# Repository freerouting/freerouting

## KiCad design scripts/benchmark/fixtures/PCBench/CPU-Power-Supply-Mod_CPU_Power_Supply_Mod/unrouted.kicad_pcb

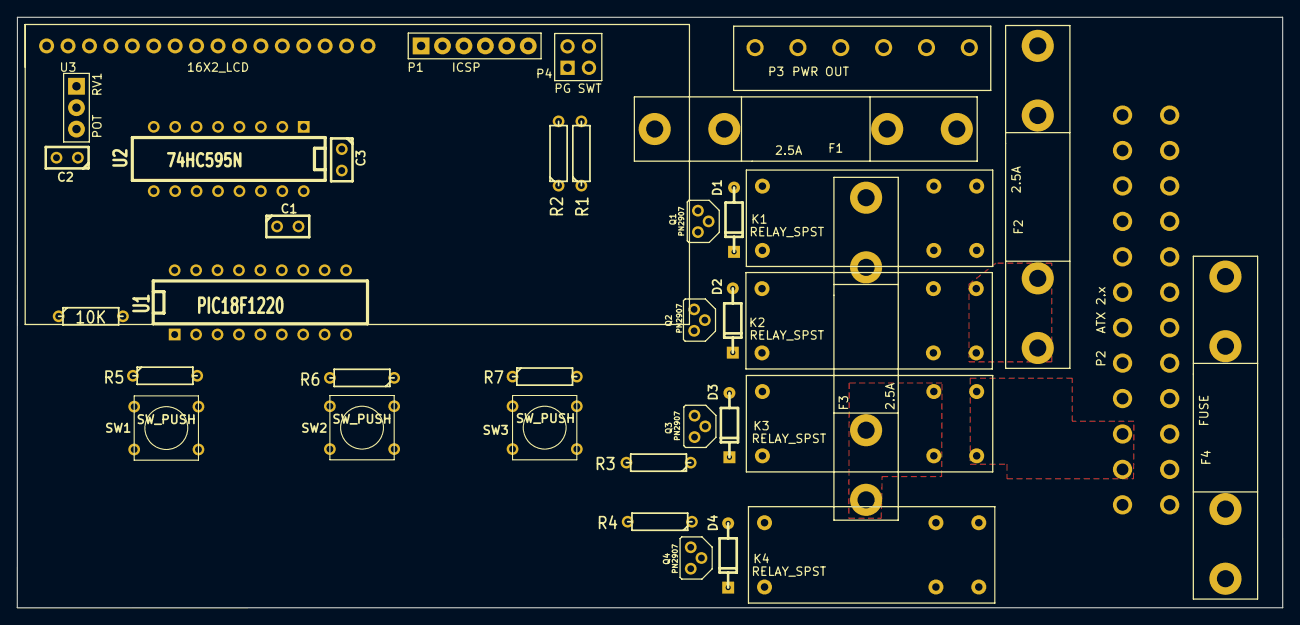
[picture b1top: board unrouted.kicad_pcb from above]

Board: 2 copper layers, 150.0 x 70.0 mm, 38 parts (0 on the bottom side), 49 nets, no tracks yet.

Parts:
C1, C2, C3: 100n; C1
D1, D2, D3, D4: DIODE; DO-35
F1, F2, F3: 2.5A; FUSE
F4: FUSE
K1, K2, K3, K4: RELAY_SPST
P1: ICSP; CON_6x1
P2: ATX 2.x; ATX-24PIN
P3: PWR OUT; 1.27mm_CON
P4: PG SWT; CON_2x2
Q1, Q2, Q3, Q4: PN2907; TO92PN
R1, R2, R3, R4, R5, R6, R7: R; R3
R8: 10K; R3
RV1: POT; CON_3x1
SW1, SW2, SW3: SW_PUSH; SW_PUSH_SMALL
U1: PIC18F1220; DIP-18__300
U2: 74HC595N; DIP-16__300
U3: 16X2_LCD; 1602A_LCD

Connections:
+3.3V: K1.2, P2.1, P2.2, P2.12, P2.13
+5V: F2.1, P2.4, P2.6, P2.21, P2.22, P2.23
+5VA: C1.1, C2.2, C3.2, P1.2, P2.9, Q1.1, Q2.1, Q3.1, Q4.1, R8.1, RV1.1, SW1.1, SW2.1, SW3.1, U1.14, U2.10, U2.16, U3.2, U3.15
+12V: K3.2, P2.10, P2.11
-12V: F4.1, P2.14
/ON1: Q1.2, R1.1
/ON2: Q2.2, R2.1
/ON3: Q3.2, R3.1
/ON4: Q4.2, R4.1
/PG: P2.8, U1.7
/PGC: P1.5, P4.3, U1.12
/PGD: P1.4, P4.1, U1.13
/PN: P2.16, U1.6
/SW1: R5.2, SW1.2, U1.1
/SW2: R6.2, SW2.2, U1.2
/SW3: R7.2, SW3.2, U1.3
GND: C1.2, C2.1, C3.1, D1.1, D2.1, D3.1, D4.1, K1.3, K2.3, K3.3, K4.3, P1.3, P2.3, P2.5, P2.7, P2.15, P2.17, P2.18, P2.19, P2.24, P3.1, P3.4, R5.1, R6.1, R7.1, RV1.3, U1.5, U2.8, U2.13, U3.1, U3.16
unnamed: P1.1, R8.2, U1.4
unnamed: RV1.2, U3.3
unnamed: U2.15, U3.14
unnamed: U2.1, U3.13
unnamed: U2.2, U3.12
unnamed: U2.3, U3.11
unnamed: U2.4, U3.10
unnamed: U2.5, U3.9
unnamed: U2.6, U3.8
unnamed: U2.7, U3.7
unnamed: U1.18, U3.6
unnamed: U1.10, U3.4
unnamed: U1.11, U3.5
unnamed: U1.15, U2.14
unnamed: U1.16, U2.12
unnamed: U1.17, U2.11
unnamed: F3.1, P3.3
unnamed: F2.2, K2.2
unnamed: P4.4, R2.2
unnamed: P4.2, R1.2
unnamed: D3.2, K3.4, Q3.3
unnamed: F4.2, K4.2
unnamed: D4.2, K4.4, Q4.3
unnamed: K4.1, P3.6
unnamed: D2.2, K2.4, Q2.3
unnamed: D1.2, K1.4, Q1.3
unnamed: F1.1, P3.2
unnamed: R4.2, U1.8
unnamed: R3.2, U1.9
unnamed: F1.2, K1.1
unnamed: K2.1, P3.5
unnamed: F3.2, K3.1

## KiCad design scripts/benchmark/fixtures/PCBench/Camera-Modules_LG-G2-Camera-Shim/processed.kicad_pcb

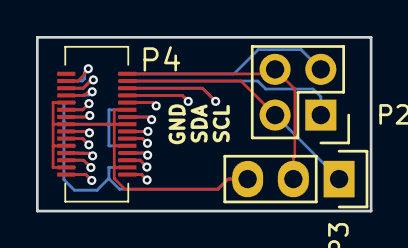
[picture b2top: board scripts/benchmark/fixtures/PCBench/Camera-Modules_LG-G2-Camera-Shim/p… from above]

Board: 2 copper layers, 18.5 x 9.7 mm, 4 parts (1 on the bottom side), 24 nets.

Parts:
P1: LG-G2-G3-Rear-Camera; GB042-30P
P2: CONN_02X02; Pin_Header_Straight_2x02
P3: CONN_01X03; Pin_Header_Straight_1x03
P4: LG-G2-G3-Rear-Camera; GB042-30S

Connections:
/+1V0_VREG_L3: P1.28, P4.28
/+1V8_13M_VCM: P1.3, P4.3
/+1V8_13M_VDDIO: P1.27, P4.27
/+2V7_13M_ANA: P1.16, P4.16
/+2V8_OIS_ANA: P1.15, P4.15
/+2V8_OIS_DIG: P1.4, P4.4
/CAM_MCLK: P1.24, P4.24
/CAM_RESET_N: P1.26, P4.26
/CAM_SCL: P2.2, P3.1, P4.29
/CAM_SDA: P2.4, P3.2, P4.30
/CLK_N: P1.13, P4.13
/CLK_P: P1.12, P4.12
/DATA0_N: P1.10, P4.10
/DATA0_P: P1.9, P4.9
/DATA1_N: P1.7, P4.7
/DATA1_P: P1.6, P4.6
/DATA2_N: P1.18, P4.18
/DATA2_P: P1.19, P4.19
/DATA3_N: P1.21, P4.21
/DATA3_P: P1.22, P4.22
/OIS_RESET_N: P1.2, P4.2
/PHONE_SCL: P1.29, P2.1
/PHONE_SDA: P1.30, P2.3
GND: P1.5, P1.8, P1.11, P1.14, P1.17, P1.20, P1.23, P1.25, P3.3, P4.5, P4.8, P4.11, P4.14, P4.17, P4.20, P4.23, P4.25

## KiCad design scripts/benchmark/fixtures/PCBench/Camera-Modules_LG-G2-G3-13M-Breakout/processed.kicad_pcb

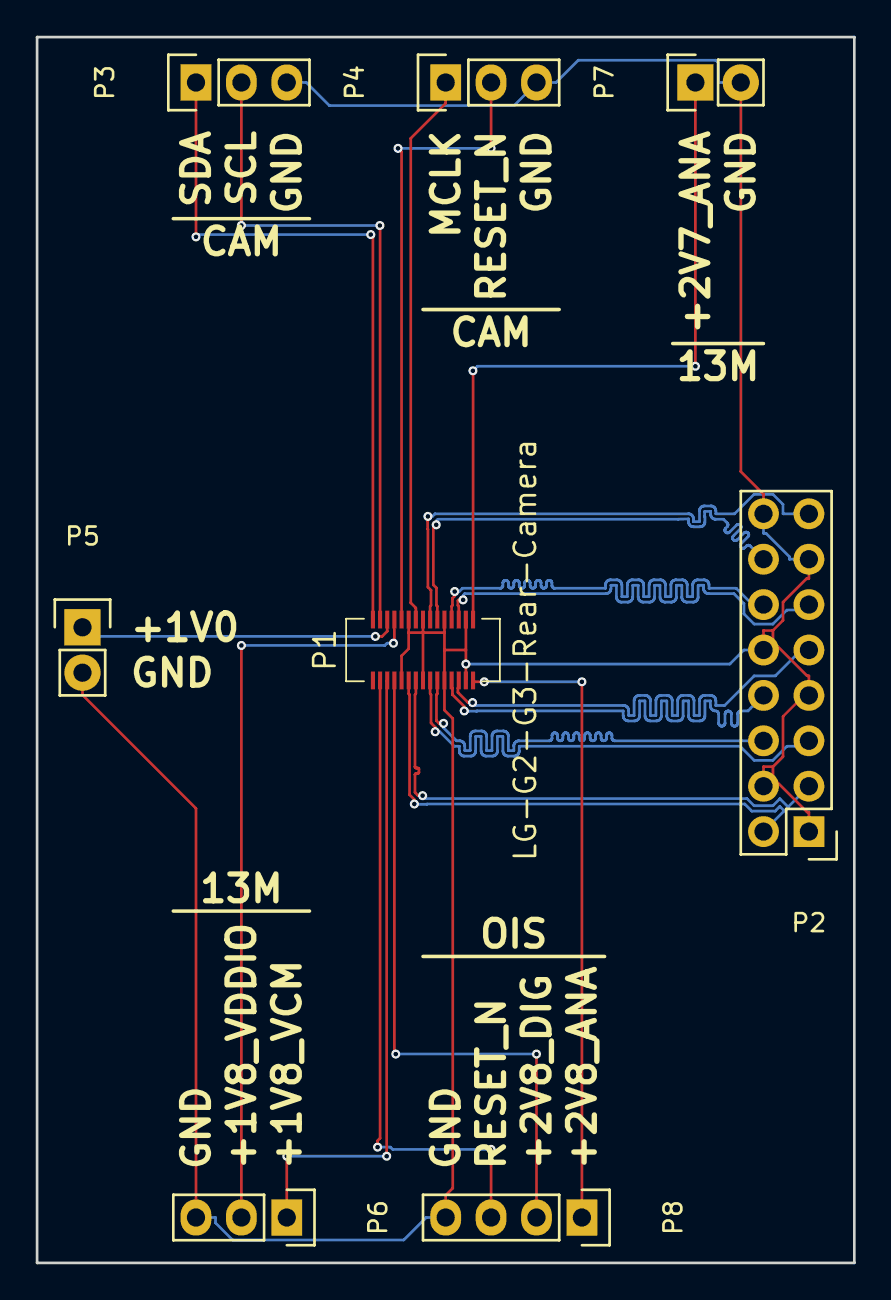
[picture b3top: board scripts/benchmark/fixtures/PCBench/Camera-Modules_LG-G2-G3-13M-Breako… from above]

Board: 2 copper layers, 45.7 x 68.6 mm, 8 parts (0 on the bottom side), 22 nets.

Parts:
P1: LG-G2-G3-Rear-Camera; GB042-30S
P2: CONN_02X08; Pin_Header_Straight_2x08
P3, P4, P6: CONN_01X03; Pin_Header_Straight_1x03
P5, P7: CONN_01X02; Pin_Header_Straight_1x02
P8: CONN_01X04; Pin_Header_Straight_1x04

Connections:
/+1V0_VREG_L3: P1.28, P5.1
/+1V8_13M_VCM: P1.3, P6.1
/+1V8_13M_VDDIO: P1.27, P6.2
/+2V7_13M_ANA: P1.16, P7.1
/+2V8_OIS_ANA: P1.15, P8.1
/+2V8_OIS_DIG: P1.4, P8.2
/CAM_MCLK: P1.24, P4.1
/CAM_RESET_N: P1.26, P4.2
/CAM_SCL: P1.29, P3.2
/CAM_SDA: P1.30, P3.1
/CLK_N: P1.13, P2.9
/CLK_P: P1.12, P2.8
/DATA0_N: P1.10, P2.6
/DATA0_P: P1.9, P2.5
/DATA1_N: P1.7, P2.3
/DATA1_P: P1.6, P2.2
/DATA2_N: P1.18, P2.11
/DATA2_P: P1.19, P2.12
/DATA3_N: P1.21, P2.14
/DATA3_P: P1.22, P2.15
/OIS_RESET_N: P1.2, P8.3
GND: P1.5, P1.8, P1.11, P1.14, P1.17, P1.20, P1.23, P1.25, P2.1, P2.4, P2.7, P2.10, P2.13, P2.16, P3.3, P4.3, P5.2, P6.3, P7.2, P8.4

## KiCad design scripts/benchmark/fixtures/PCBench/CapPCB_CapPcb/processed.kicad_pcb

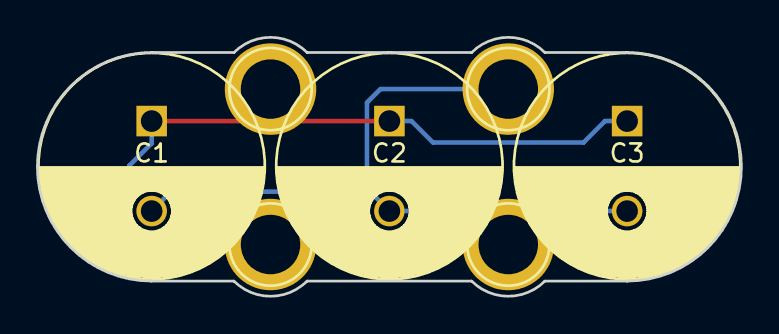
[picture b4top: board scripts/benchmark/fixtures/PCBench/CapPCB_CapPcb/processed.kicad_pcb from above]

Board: 2 copper layers, 39.1 x 14.4 mm, 7 parts (0 on the bottom side), 2 nets.

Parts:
C1, C2, C3: 560uF, 63V; C_Radial_D12.5_L25_P5
P1, P3: +; 1pin
P2, P4: -; 1pin

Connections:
unnamed: C1.1, C2.1, C3.1, P1.1, P3.1
unnamed: C1.2, C2.2, C3.2, P2.1, P4.1
